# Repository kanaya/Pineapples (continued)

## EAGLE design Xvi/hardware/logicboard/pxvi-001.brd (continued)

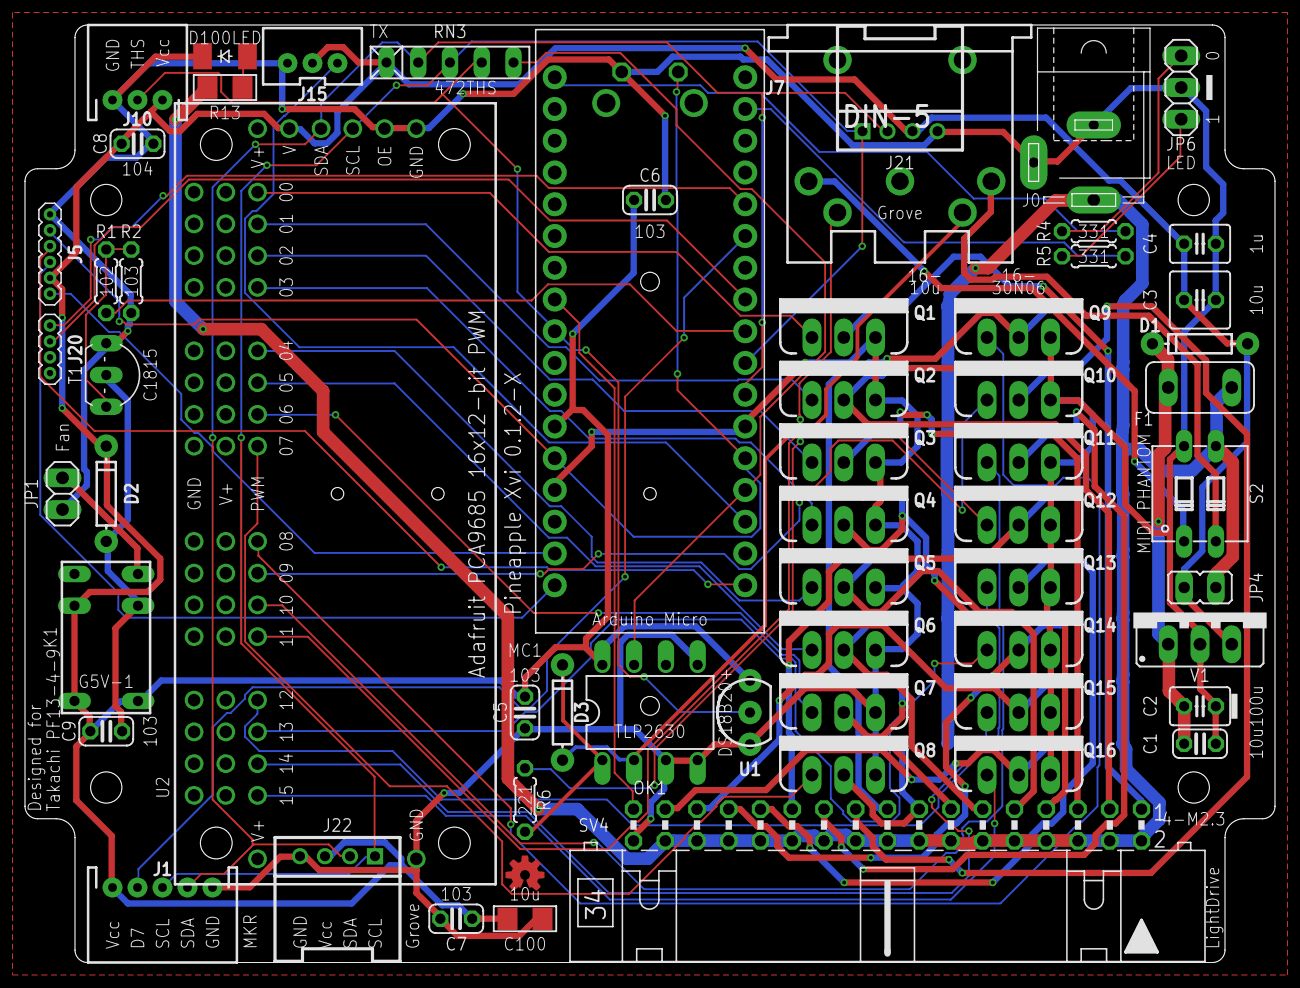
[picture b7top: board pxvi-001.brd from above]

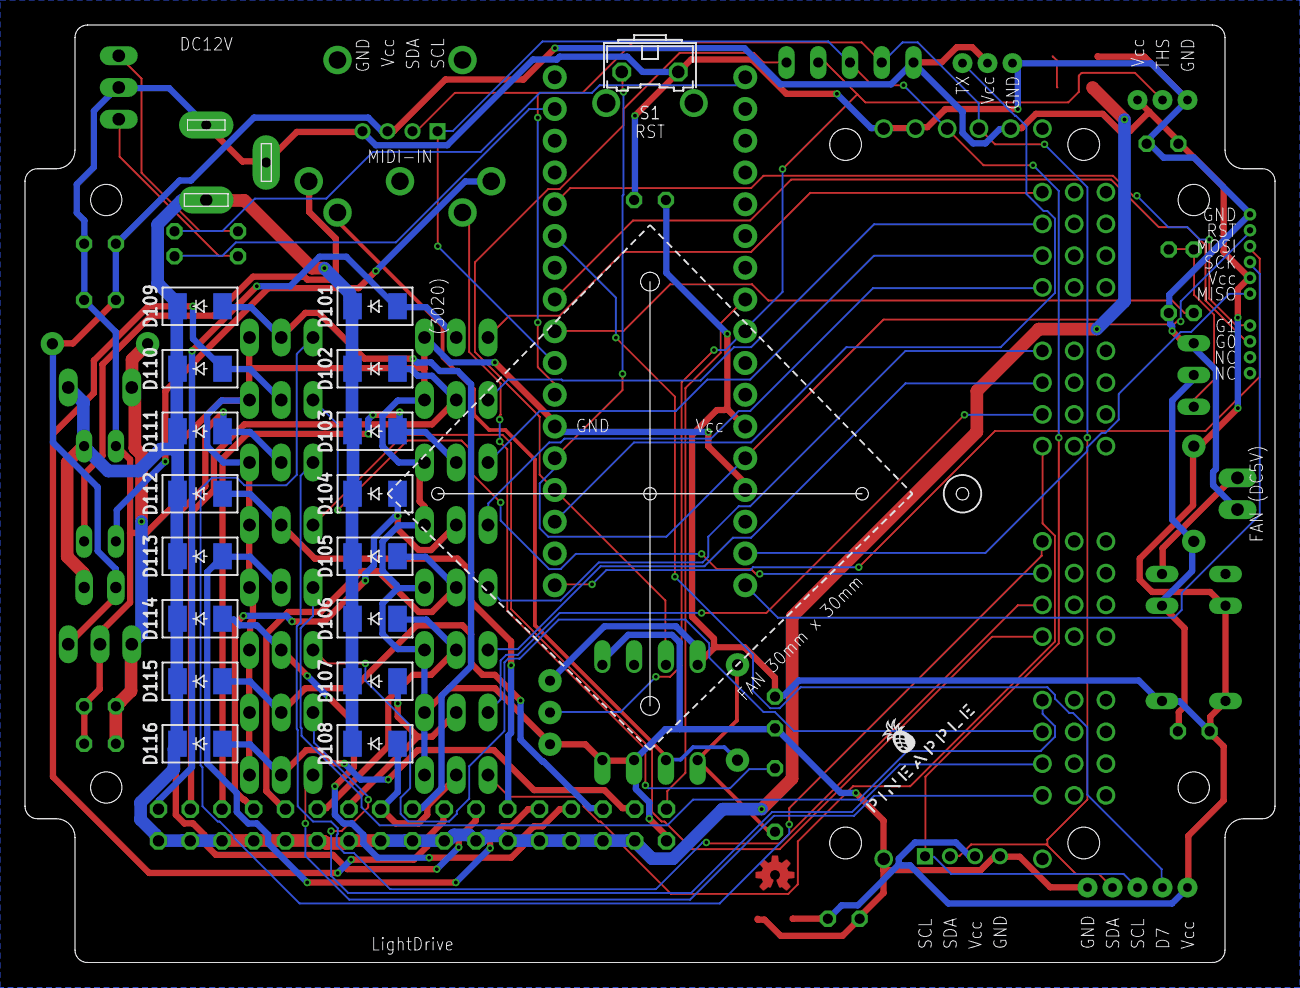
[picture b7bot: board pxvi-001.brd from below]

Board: 2 copper layers, 100.0 x 75.0 mm, 78 parts (18 on the bottom side), 63 nets.

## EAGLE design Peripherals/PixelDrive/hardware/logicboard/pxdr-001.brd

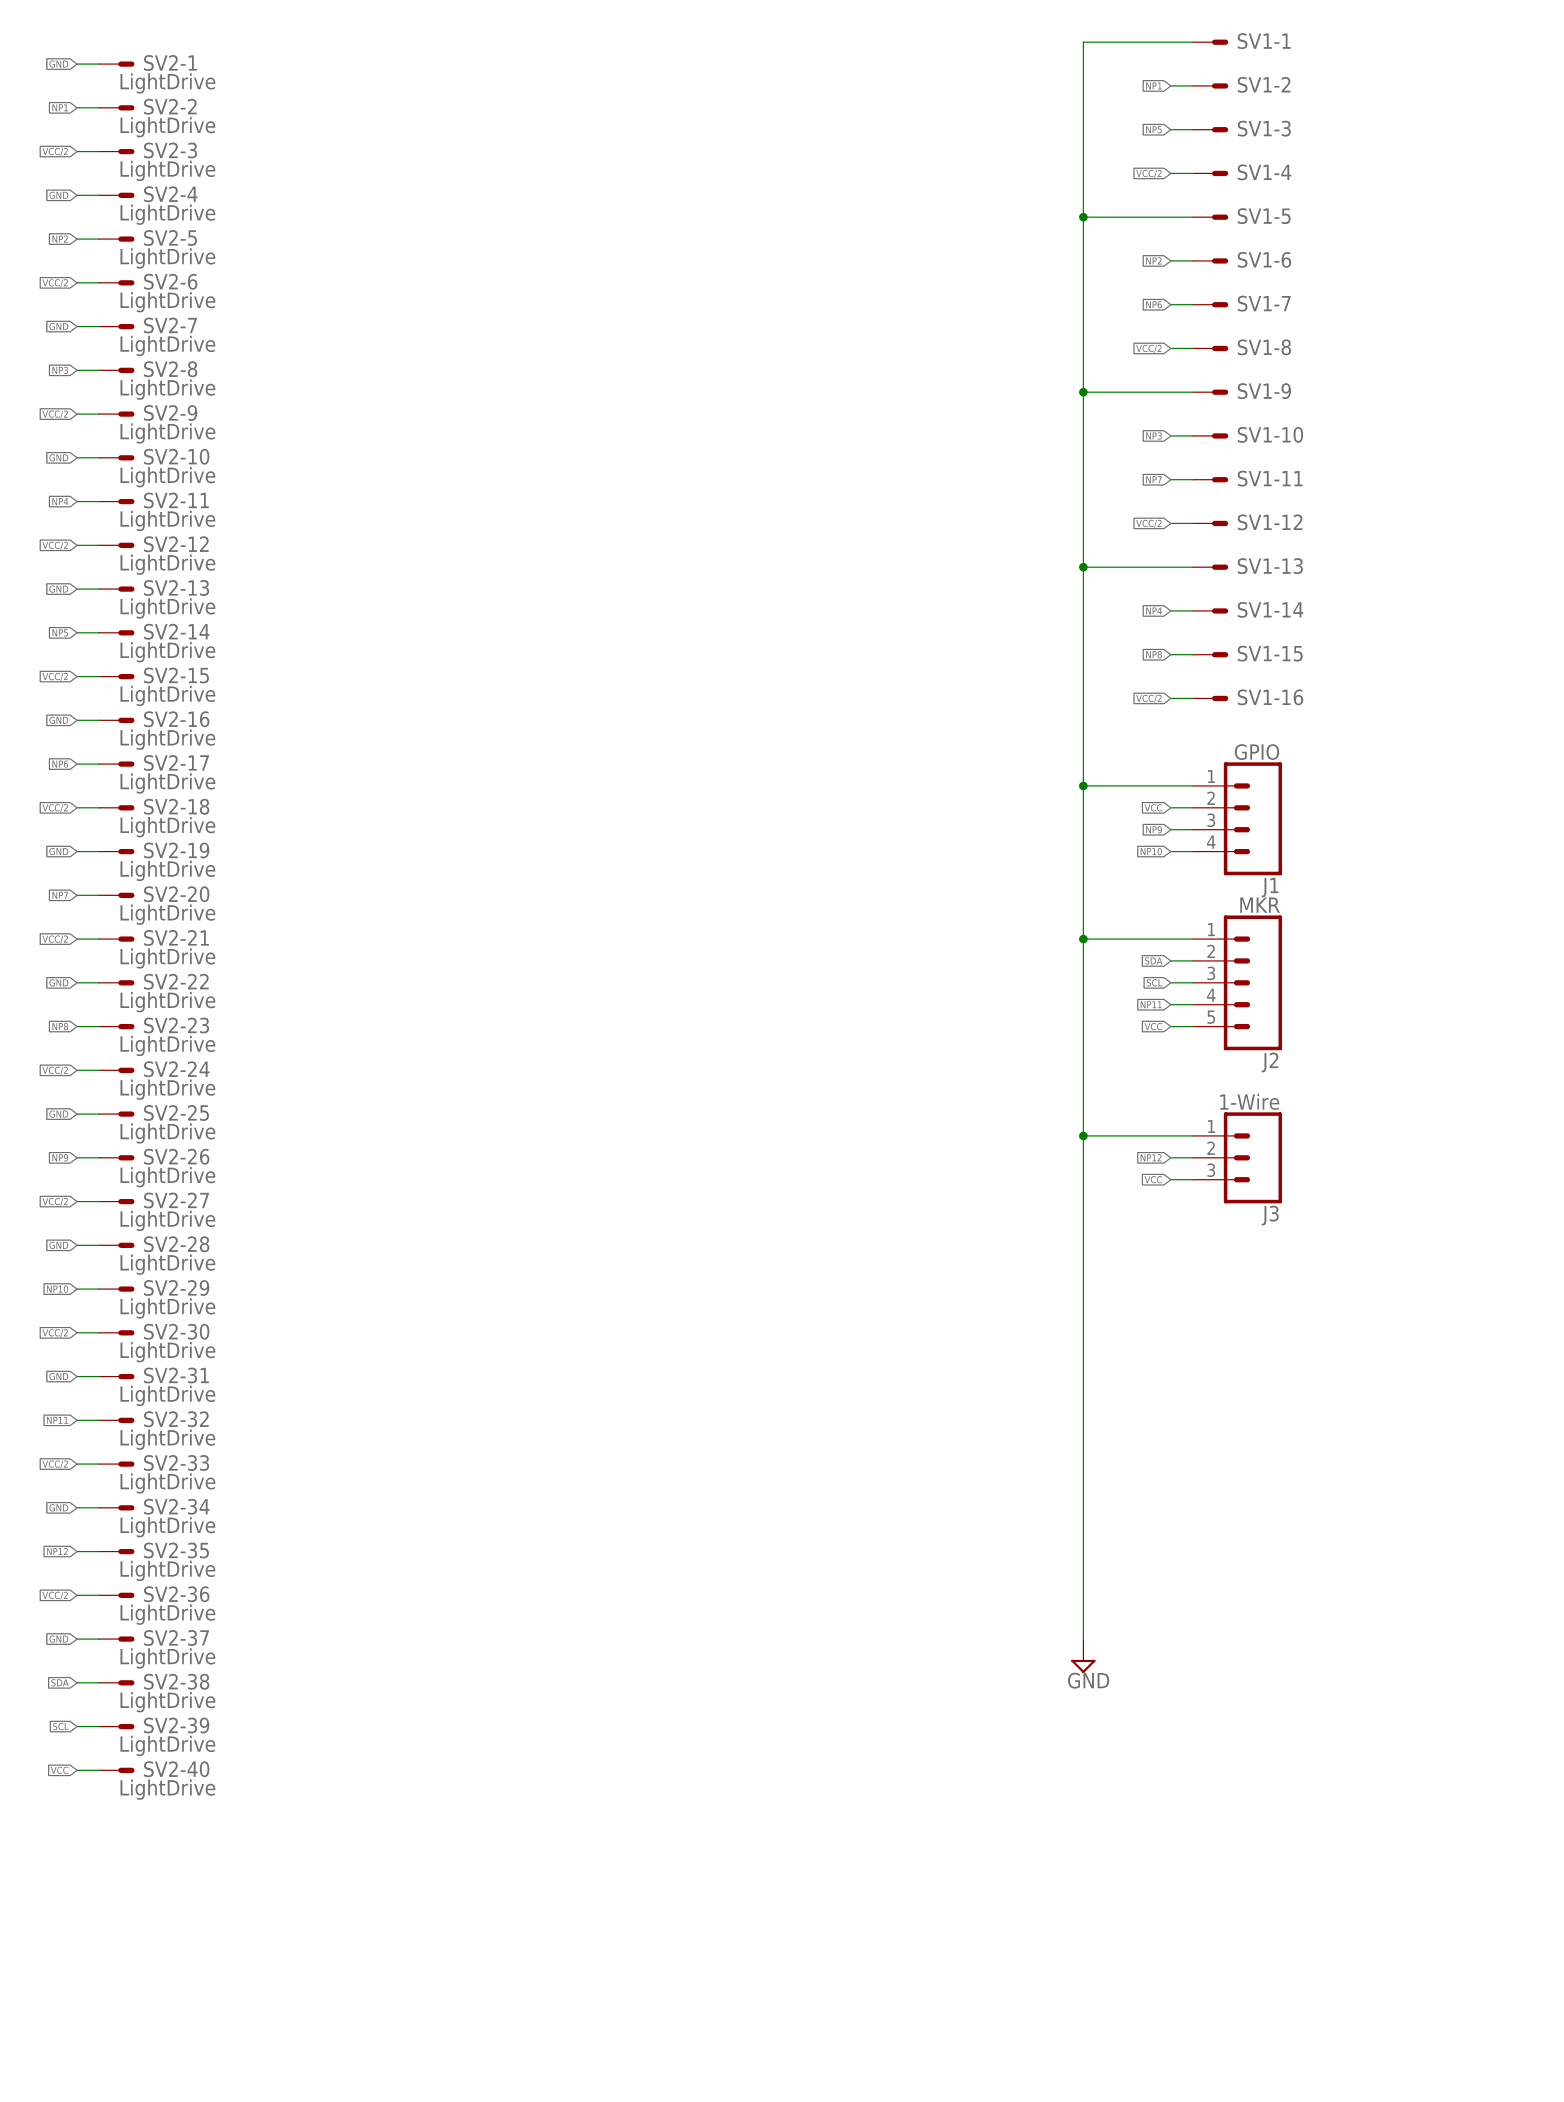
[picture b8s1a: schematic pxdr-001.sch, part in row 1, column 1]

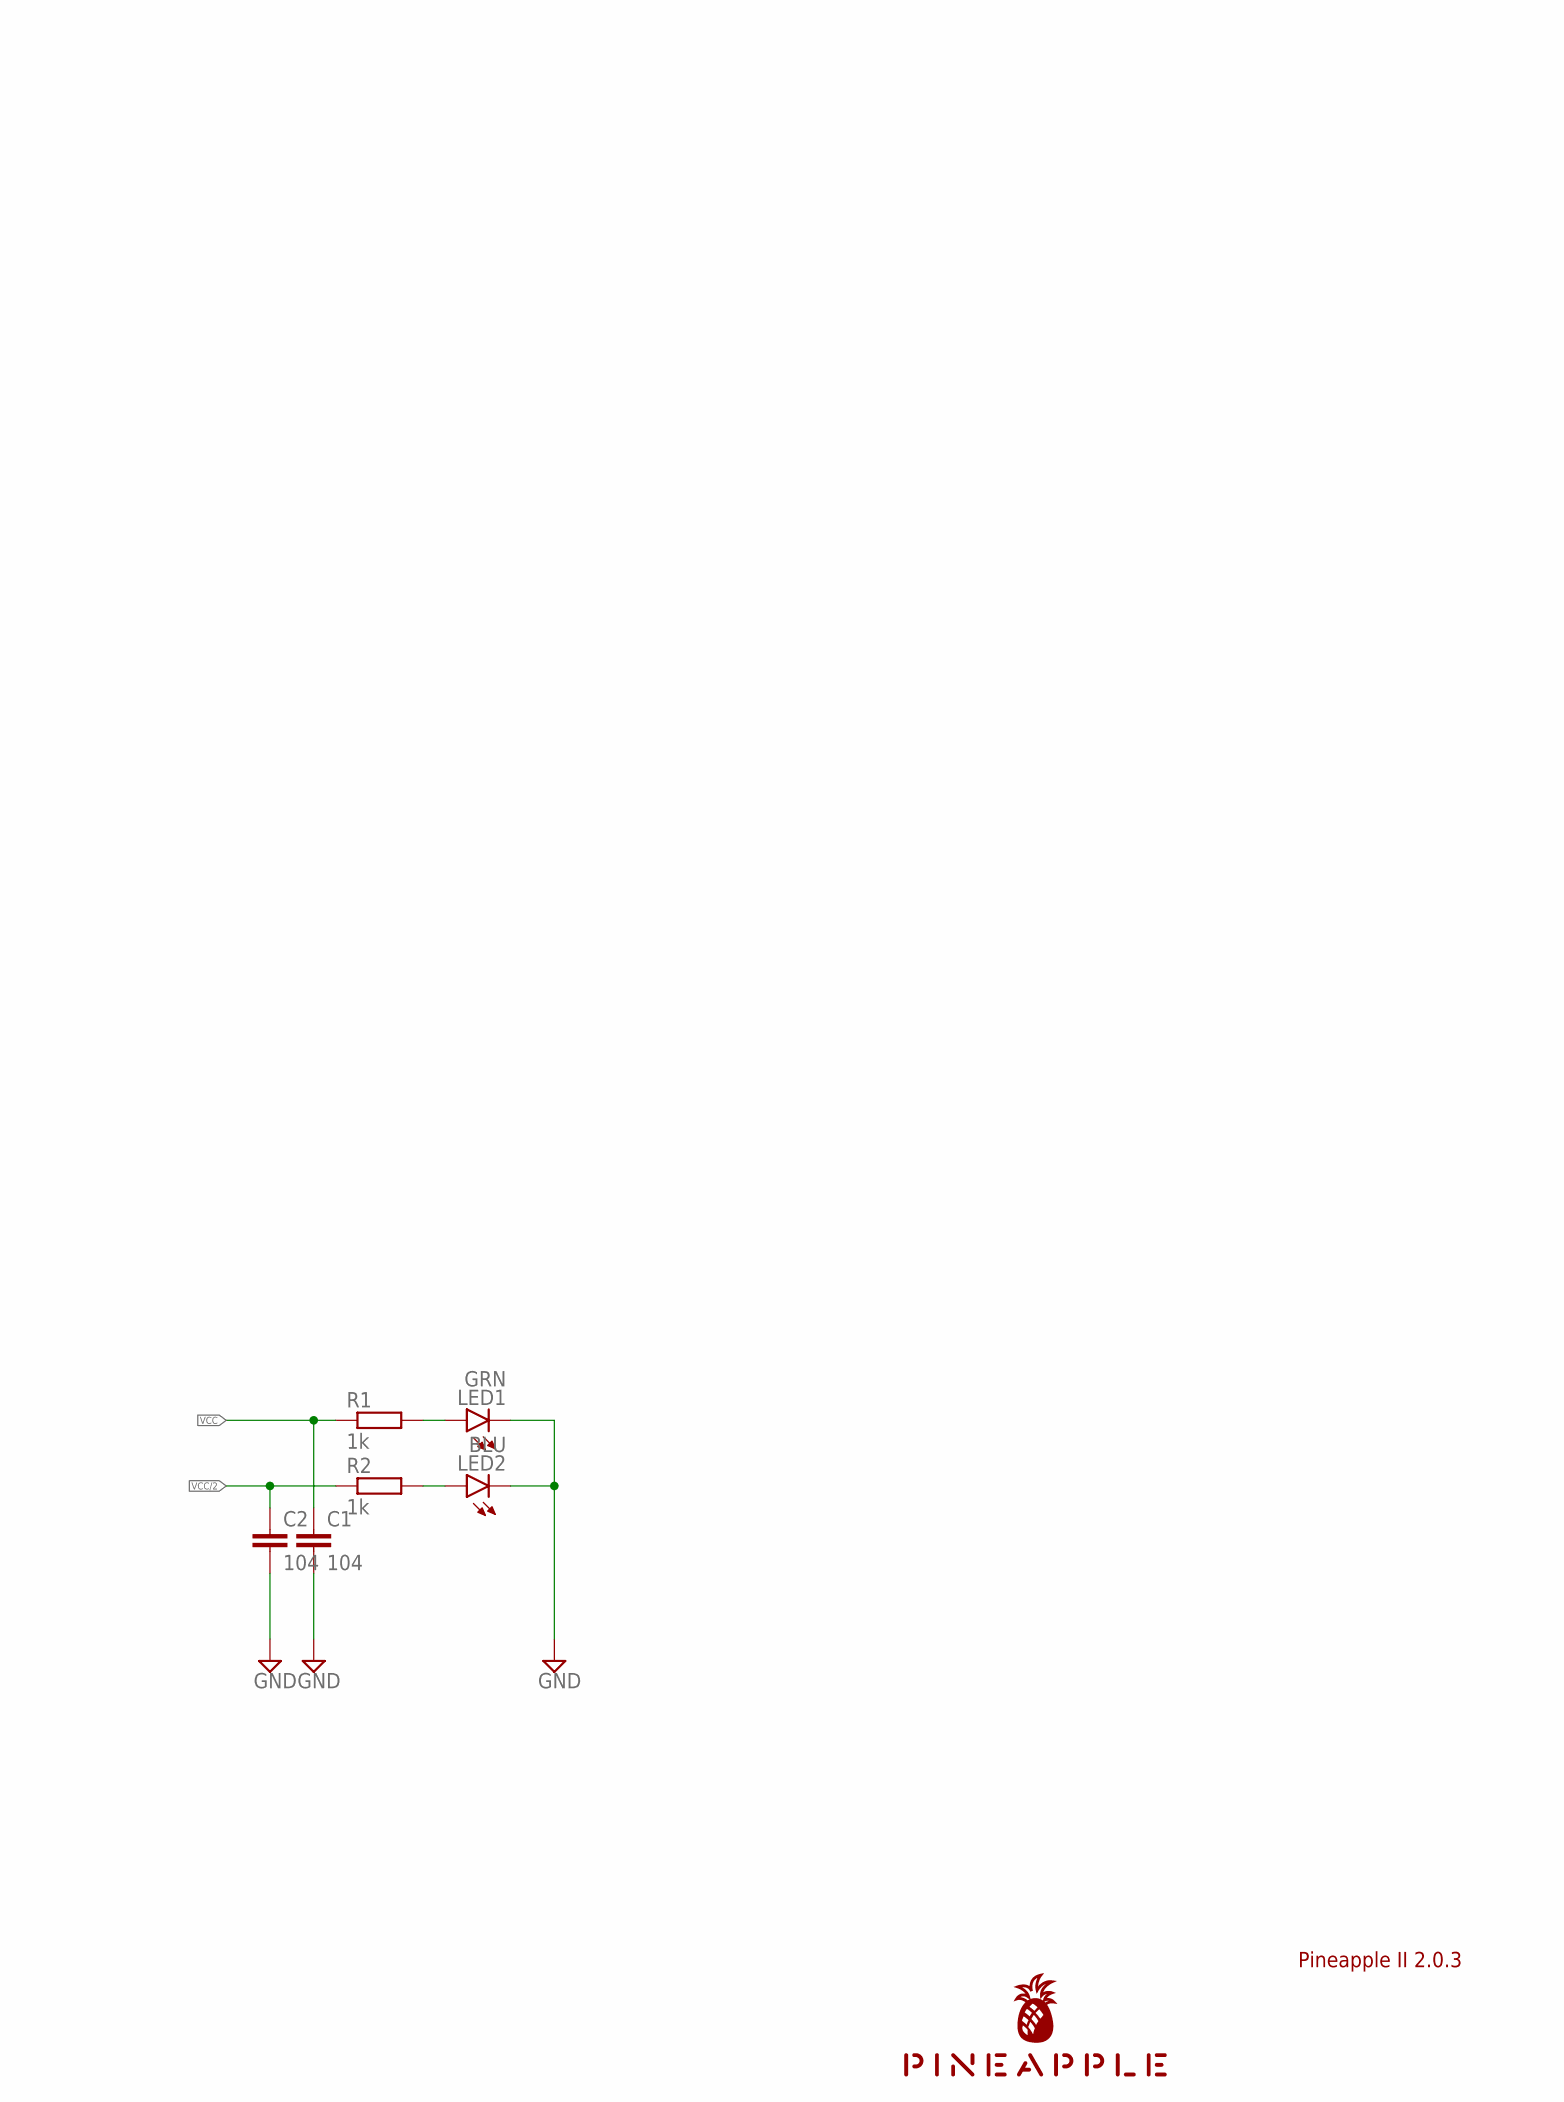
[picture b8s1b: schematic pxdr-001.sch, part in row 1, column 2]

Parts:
C1, C2: 104; C025-025X050
J1: GPIO; JST-4-PTH
J2: MKR; JST-5-PTH
J3: 1-Wire; JST-3-PTH
LED1: GRN; Q62902-B152
LED2: BLU; Q62902-B152
R1, R2: 1k; 0204/5
SV1: ML16LE; ML16L
SV2: LightDrive; ML40L
U$1: PINEAPPLE450_SILK

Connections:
GND: C1.2, C2.2, J1.1, J2.1, J3.1, LED1.K (C), LED2.K (C), SV1.1, SV1.5, SV1.9, SV1.13, SV2.1, SV2.4, SV2.7, SV2.10, SV2.13, SV2.16, SV2.19, SV2.22, SV2.25, SV2.28, SV2.31, SV2.34, SV2.37
NP1: SV1.2, SV2.2
NP2: SV1.6, SV2.5
NP3: SV1.10, SV2.8
NP4: SV1.14, SV2.11
NP5: SV1.3, SV2.14
NP6: SV1.7, SV2.17
NP7: SV1.11, SV2.20
NP8: SV1.15, SV2.23
NP9: J1.3, SV2.26
NP10: J1.4, SV2.29
NP11: J2.4, SV2.32
NP12: J3.2, SV2.35
SCL: J2.3, SV2.39
SDA: J2.2, SV2.38
VCC: C1.1, J1.2, J2.5, J3.3, R1.1, SV2.40
VCC2LED: LED2.A, R2.2
VCC/2: C2.1, R2.1, SV1.4, SV1.8, SV1.12, SV1.16, SV2.3, SV2.6, SV2.9, SV2.12, SV2.15, SV2.18, SV2.21, SV2.24, SV2.27, SV2.30, SV2.33, SV2.36
VCCLED: LED1.A, R1.2

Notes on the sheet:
Pineapple II 2.0.3

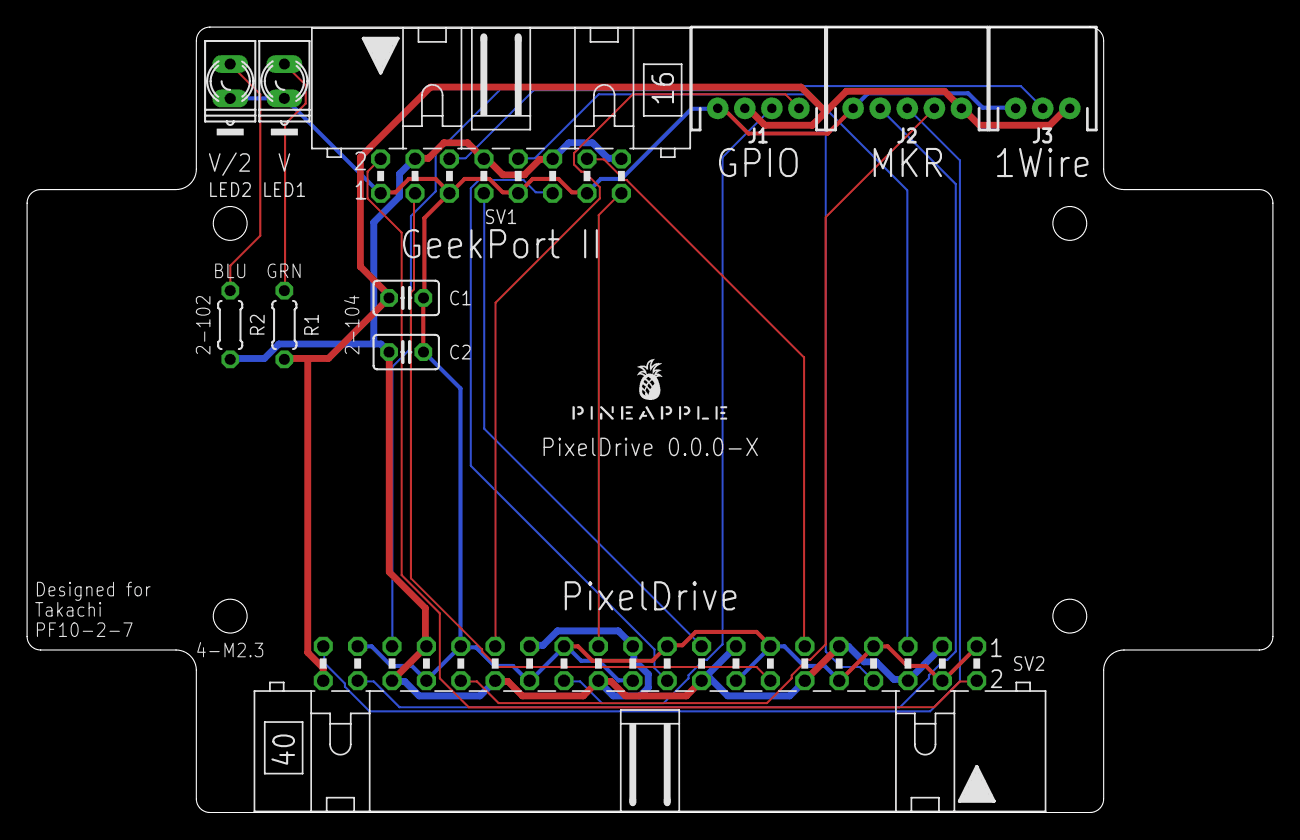
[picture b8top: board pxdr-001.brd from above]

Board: 2 copper layers, 92.0 x 58.0 mm, 12 parts (0 on the bottom side), 19 nets.

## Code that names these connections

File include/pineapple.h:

// pineapple.h

const int RX    = 0;
const int TX    = 1;
const int SDA   = 2;
const int SCL   = 3;
const int RLY   = 4;
const int GPIO0 = 5;   // PWM
const int DTCT0 = 6;
const int GP_R  = 6;   // PWM
const int D7    = 7;
const int GATE  = 7;
const int GPIO1 = 8;   // PWM
const int DTCT1 = 9;
const int GP_G  = 9;   // PWM
const int DTCT2 = 10;
const int GP_B  = 10;
const int LED1  = 11;  // PWM
const int DTCT3 = 12;
const int LED0  = 13;  // PWM
const int ANLG0 = A0;
const int ANLG1 = A1;
const int ANLG2 = A2;
const int ANLG3 = A3;
const int MNTR  = A4;
const int THS   = A5;

const int LEDS[]    = { LED0, LED1 };
const int GPIOS[]   = { GPIO0, GPIO1 };
const int DTCTS[]   = { DTCT0, DTCT1, DTCT2, DTCT3 };
const int ANLGS[]   = { ANLG0, ANLG1, ANLG2, ANLG3 };
const int GP_RGB[]  = { GP_R, GP_G, GP_B };
const int GP_PINS[] = { ANLG0, DTCT0, ANLG1, DTCT1, ANLG2, DTCT2, ANLG3, DTCT3 };

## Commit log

2022-11-26 Imported Pineapple Logo.
2022-11-26 Imported the latest commit of release/1.0.0 of GeekBox.
2022-11-26 Imported the latest commit of release/1.0.0 of MIDIBox.
2022-11-26 Imported the latest commit of MKRDisplay 1 and 2.
2022-11-26 Imported the latest commit of SuperCharger.
2022-11-26 Imported Pineapple Zero 2.6.3-B.
2022-11-26 Imported Pineapple Zero A version 0.0.1-X.
2022-11-26 Imported Pineapple I version 2.6.5-B.
2022-11-26 Imported hardware of the latest commit of support/2.7 of Pineapple II.
2022-11-26 Imported the latest commit of support/2.7 of Pineapple IIb (minor fixed version of 2.7.0-GM).
2022-11-26 Imported the latest commit of release/2.6.5 of Pineapple IIc.
2022-11-26 Imported the latest commit of release/2.6.5 of Pineapple IId.
2022-11-26 Imported the latest commit of GrovePort.
2022-11-26 Imported the latest commit of GroveGear.
2022-11-26 Imported HexGear version 0.0.1-X.
2022-11-26 Imported the latest commit of release/1.0.0 of HexSW.
2022-11-26 Imported the latest commit of RLYPort.
2022-11-26 Imported SharpGear 0.0.1-X.
2022-11-26 Imported the latest commit of release/0.0.1 of SharpPort.
2022-11-30 Fixed silk.
2022-12-02 Clean up of schematic.
2022-12-06 Clean up of schematic of P2b.
2022-12-07 Trying to add 4-pin front con.
2022-12-07 First try of USB box.
2022-12-07 New form factor.
2022-12-08 Added resistors for iPod shuffle compatibility.
2022-12-08 Routed.
2022-12-08 Fixed signal names and silk of MIDI Box.
2022-12-08 LEDSW connector (temporarily named JP4) is added.
2022-12-11 Panel design.
2022-12-13 Extra I2C conn.
2022-12-16 Changed dimension of LED hole. Recommended LED: https://akizukidenshi.com/catalog/g/gI-12411/
2023-01-05 Fixed dimension of the panel.
2023-08-19 Development of IIgs.
2023-08-20 Artwork.
2023-08-20 Adding pull-down r.
2023-08-20 Pull-down.
2023-08-20 Double Grove con.
2023-08-20 Backside silk.
2023-08-20 Silk.
2023-08-20 Rebrand. (2gs -> 1x)
2023-08-20 Rebland. (Ix -> Xvi)
2023-08-20 Merged repo of Pineapple Vii.
2023-09-09 Broaden path.
2023-09-09 Broad LD.
2023-09-09 GND pattern.
2023-09-09 Fixed.
2023-09-10 Rebuild submodules.
2023-09-25 Changed version number on the silk.
2023-09-26 Thermal sensor and drill hole guide.
2023-09-26 Added silk for fan.
2023-09-27 Monitor.
2023-09-29 Guide for fan.
2023-10-04 Xvi/LightDrive Port.
2023-10-11 Redesign.
2023-10-11 Arrangement.
2023-10-11 Diodes -> back.
2023-10-11 Relay.
2023-10-11 Qwiic con.
2023-10-12 Added THS connector.
2023-10-13 RST pin.
2023-10-14 Cap and diode.
2023-10-14 Wired.
2023-10-14 Re-routed.
2023-10-15 Added fuse.
2023-10-15 Signal names.
2023-10-15 ANLG and DTCT pads.
2023-10-16 Added TX.
2023-10-17 Fixed positioning error of Monitor for PXVI.
2023-10-18 Fixed monitor board.
2023-10-20 Fixed positions of the components.
2023-10-21 Pineapple candy.
2023-10-21 Silk and hole.
2023-10-21 Optocoupler.
2023-10-21 Routing.
2023-10-31 Header file.
2023-10-31 Fixed typo.
2023-11-05 The first Sweetio.
2023-11-05 Moved JP00.
2023-11-05 RST switch.
2023-11-05 RST Sw.
2023-11-05 Added RST sw to P2b.
2023-11-05 Front Grove conn.
2023-11-08 Fixed back-side silk.
2023-11-08 Changed pads to Inf-ohm chip resistor.
2023-11-12 Triple MIDI transmitter/receiver.
2023-11-12 Removed conventional circuit.
2023-11-13 Layout.
2023-11-13 Fixed layout.
2023-11-13 RX indicators.
2023-11-18 Fixed signaling.
2023-11-24 Replaced Rs with RN.
2023-11-24 Fixed P2b.
2023-11-25 Fixed Xvi.
2023-11-25 Fixed Sweetio.
2023-11-25 Fixed wiring of 0.
2023-11-26 0b initial design.
2023-11-26 Now runs by 7805 regulator.
2023-11-26 Fixed pinout of 0b.
2023-11-26 Fixed caps.
2023-11-26 Now P2b has phantom power.
2023-11-26 Fixed bugs.
2023-11-27 Added SW.
2023-11-27 Now has a phantom SW.
2023-11-27 MIDI Phantom.
2023-11-28 Now 0b are divided in type a (straight) and type b (cross).
2023-11-29 Clean up of p0b-001.
2023-11-29 Clean up of p0b-002.
2023-11-29 Added Direct-5V resistor pattern.
2023-12-01 Dual LEDs.
2023-12-01 Rename.
2023-12-01 Pinhead.
2023-12-02 Added PoE R.
2023-12-03 Xbar.
2023-12-03 vdd/vcc xbar for lcd monitor.
2023-12-03 Added poly sw.
2023-12-04 Removed 0b type B.
2023-12-11 Start of PixelDrive.
2023-12-11 First try.
2023-12-12 Second shot.
2023-12-12 Third shot.
2024-01-08 PoE.
2024-01-08 Fixed some errors.
2024-01-08 Added Magnetic peripheral.
2024-01-14 Fixed version number of Silk. (Sweetio)
2024-02-10 Pineapple Vii v2.
2024-02-11 1st try.
2024-02-11 Added 5V-direct-injection mode.
2024-02-11 5V direct injection pins.
2024-02-11 Trial. Needs re-number of some parts.
2024-02-11 Renumbered.
2024-02-18 GroveGear -> ServoGear.
2024-02-20 Copied from 2d.
2024-12-11 Created Bellini by copying Sweetio.
2024-12-11 Prototyping...
2024-12-11 Changed dimension.
2024-12-13 Cleaning.
2024-12-15 Fixed errors.
2024-12-15 Fixed direction of Pi RTC.
2024-12-15 Copied 001 to 000.
2024-12-15 000.
2024-12-17 Bellini 002.
2025-07-18 Merged PineappleCake.
2025-07-20 Belini 2 (?).
